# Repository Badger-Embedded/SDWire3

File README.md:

# SDWire3 Flex

## This project is the fork of [SD Swap](https://github.com/Mr-Bossman/SD_Swap) project. The development tool which swaps an SD card between a USB3 card reader and a DUT.

### About

SDWire3 allows reflashing of an SD card connected to the DUT (Device Under Test), without physical contact with the device. The board is designed in such way that it fits into micro SD card slots. Thanks to this, there is no need for special cables with a micro SD adapter, though it may be beneficial to add an extention to avoid accidentally breaking your boards SD connector if someone yanks the cable.

Design is changed to have flex cable instead of solid pcb as dummy sdcard which will be connected to DUT.

**IMPORTANT**

Faster SD cards may not work on some single board computers as the
timing and capacitance on the SBC side is not right.

### Rational

After seeing the [SDWire](https://wiki.tizen.org/SDWire) project I was disappointed by the complexity as well as the lack of USB3. So this project is uses the REALTEK RTS5306E controller which many USB3 to SD adapters use. The chip has power suspend functionality which we can use as a GPIO for switching hosts. The suspend option will shut off the SD cards power but not the controllers; it also has build-in RW protection as to finish writes before switching to the SBC

The SDWire project uses a USB to GPIO chip for this, but they have two power controlled USB ports on the board as well as the above mentioned method.

### Software

To swap the SD card between the host PC and the SBC you run
`sdswap 0` or `sdswap 1`.

`1` is the host PC while `0` is the SBC. You can also chose which device to use if you have multiple attached. To do this run `sdswap 1` to print the found devices and type `sdswap 1-4 1` or another USB number. I have future plans to write this script for Windows and OSX.

```
$ sdswap -h

To switch the SD card to USB run:
sdswap 1
To switch the SD card to SBC run:
sdswap 0
To print the block dev run:
sdswap p

If you have multiple devices run either of the above.
Then run with the last param the same as above:
sdswap $(Your USB number) 0

NOTE:
When printing the block device the script waits until the device exists

Examples:
# sdswap 0
Uisng device /sys/bus/usb/devices/3-4

# sdswap 0
Uisng device /sys/bus/usb/devices/3-4
Already off.

# sdswap p
/dev/sda

# sdswap 0
Multiple devices found! Pass a usb number as param 1...
Usb num: 3-4
Usb num: 3-1

# sdswap 3-1 0
Uisng device /sys/bus/usb/devices/3-1
```

To manually controll the port use:

```
export YOUR_USB_NUM="1-4" #hub1 port4
echo 0 | sudo tee /sys/bus/usb/devices/${YOUR_USB_NUM}/power/autosuspend_delay_ms
echo auto | sudo tee /sys/bus/usb/devices/${YOUR_USB_NUM}/power/control

echo SBC
echo ${YOUR_USB_NUM} | sudo tee /sys/bus/usb/drivers/usb/unbind

echo PC
echo ${YOUR_USB_NUM} | sudo tee /sys/bus/usb/drivers/usb/bind
```

### Hardware

#### LEDs

- D2 is the **red/blue** status LED it will be **blue** when the in passthrough mode, and **red** when the USB3 controller is reading/writing to it.
- D1 is the **yellow** activity LED and blinks when the USB3 controller is reading/writing.
- D3 is the **red** power LED and is active when the USB3 controller has power.

**NOTE**: The **red** power LED will not be on if the USB cable isn't 5V providing power.

### TODO

- Fix SBC side timeing
- Write script for Windows and OSX.
- Edit pick n' place csv
- Label stat leds
- Add use switching regulator
- Add E-Fuse
- Update readme

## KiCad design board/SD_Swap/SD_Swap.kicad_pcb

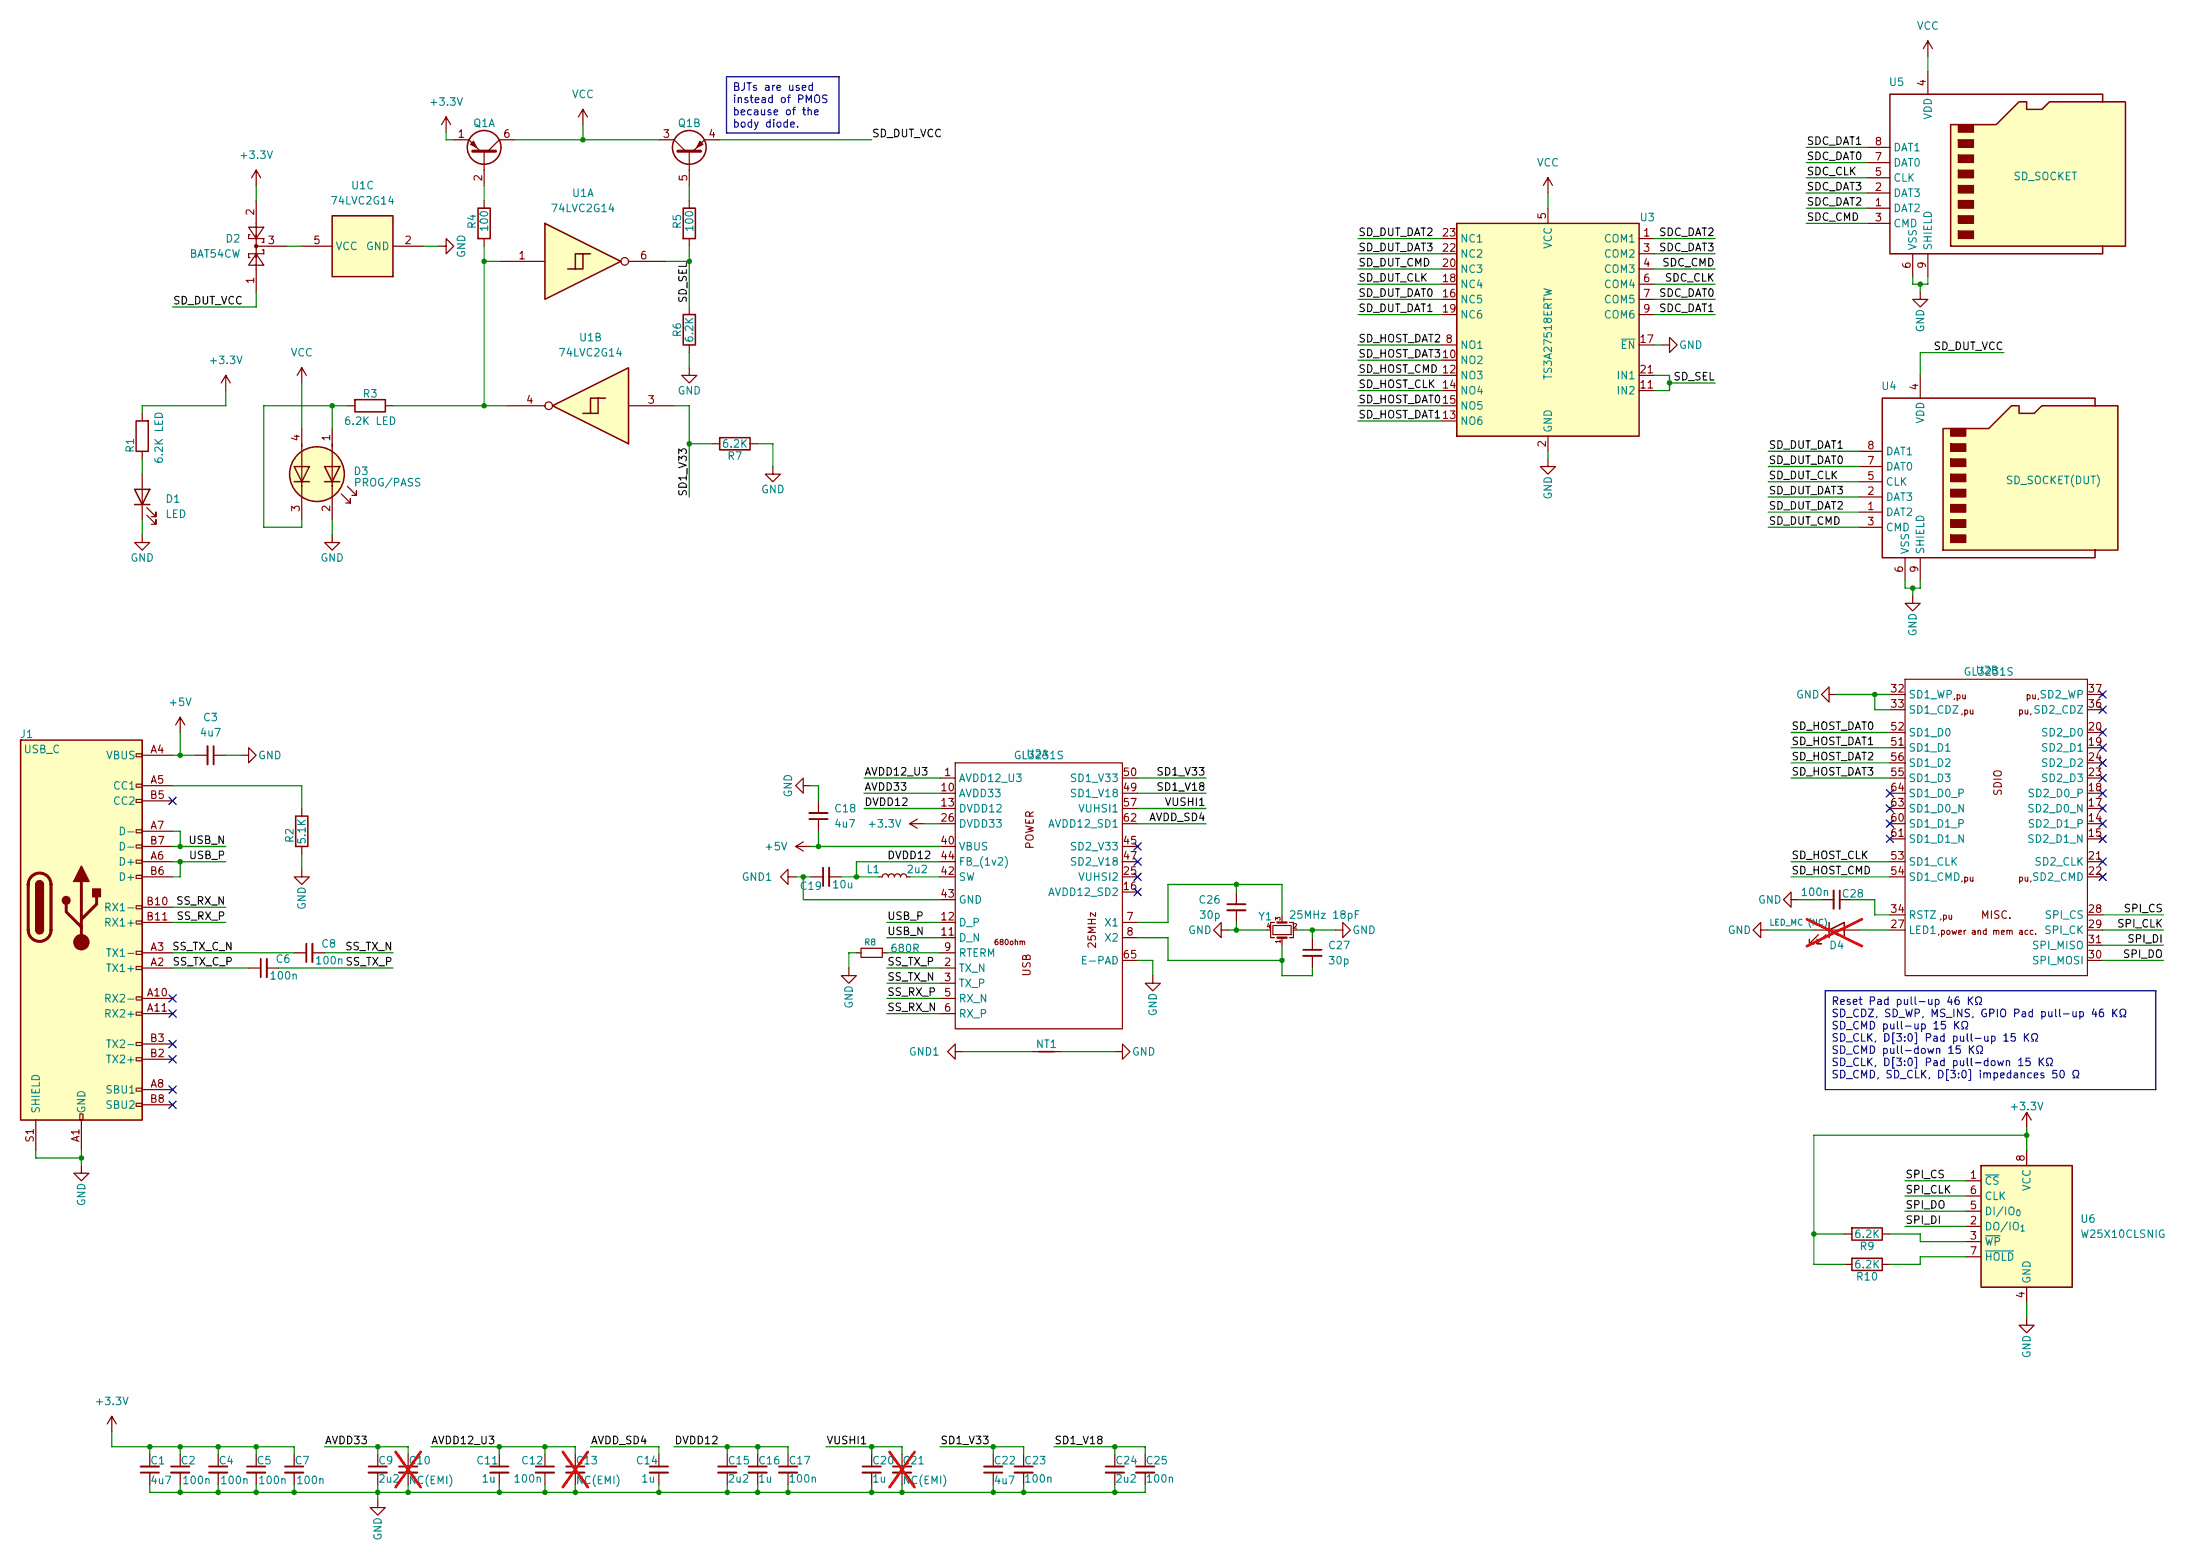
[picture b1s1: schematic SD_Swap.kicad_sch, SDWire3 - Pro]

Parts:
C1, C3, C18, C22: 4u7; C_0402_1005Metric; LCSC C23733
C2, C4, C5, C6, C7, C8, C12, C17, C23, C25, C28: 100n; C_0201_0603Metric; LCSC C66938
C9, C15, C24: 2u2; C_0201_0603Metric; LCSC C76933
C10, C13, C21: NC(EMI); C_0201_0603Metric; not fitted
C11, C14, C16, C20: 1u; C_0402_1005Metric; LCSC C107372
C19: 10u; C_0603_1608Metric; LCSC C19702
C26, C27: 30p; C_0201_0603Metric; LCSC C384980
D1: LED; LED_0402_1005Metric; LCSC C71911
D2: BAT54CW; SOT-323_SC-70; LCSC C57891
D3: PROG/PASS; LED_RGB_1210; LCSC C264332
D4: LED_MC (NC); LED_0603_1608Metric; not fitted
J1: USB_C; USB_C_Receptacle_Amphenol_10137061-00021LF; Part Number 10137061-00021LF; LCSC C3197967
L1: 2u2; L_0402_1005Metric; LCSC C383389
NT1: NetTie_2; NetTie-2_SMD_Pad0.5mm
Q1: Q_Dual_PNP_PNP_E1B1C2E2B2C1; SOT-23-6; LCSC C111730
R1, R3: 6.2K LED; R_0402_1005Metric; LCSC C25915
R2: 5.1K; R_0201_0603Metric; LCSC C100142
R4, R5: 100; R_0201_0603Metric; LCSC C2991668
R6, R7, R9, R10: 6.2K; R_0201_0603Metric; LCSC C180341
R8: 680R; R_0201_0603Metric; LCSC C473509
U1: 74LVC2G14; SOT-363_SC-70-6; LCSC C3294721
U2: GL3231S; QFN-64-1EP_8x8mm_P0.4mm_EP6.5x6.5mm_ThermalVias; LCSC C7435977
U3: TS3A27518ERTW; WQFN-24-1EP_4x4mm_P0.5mm_EP2.6x2.6mm; Part Number TS3A27518ERTW; LCSC C2651937
U4: SD_SOCKET(DUT); 105162-0001; Part Number 105162-0001; LCSC C724031
U5: SD_SOCKET; 105162-0001; Part Number 105162-0001; LCSC C724031
U6: W25X10CLSNIG; SOIC-8_3.9x4.9mm_P1.27mm; LCSC C164120
Y1: 25MHz 18pF; Crystal_SMD_2520-4Pin_2.5x2.0mm; LCSC C255956

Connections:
+3.3V: C1.2, C2.1, C4.1, C5.1, C7.1, D2.2, Q1.1 (E1), R1.2, R9.2, R10.2, U2.26 (DVDD33), U2.39 (DVDD33), U2.46 (DVDD33), U2.48 (DVDD33), U2.58 (DVDD33), U6.8 (VCC)
+5V: C3.2, C18.1, J1.A4 (VBUS), J1.A9 (VBUS), J1.B4 (VBUS), J1.B9 (VBUS), U2.40 (VBUS), U2.41 (VBUS)
/AVDD12_U3: C11.1, C12.1, C13.1, U2.1 (AVDD12_U3), U2.4 (AVDD12_U3)
/AVDD33: C9.1, C10.1, U2.10 (AVDD33)
/AVDD_SD4: C14.1, U2.62 (AVDD12_SD1)
/DVDD12: C15.1, C16.1, C17.1, C19.2, L1.1, U2.13 (DVDD12), U2.38 (DVDD12), U2.44 (FB_(1v2)), U2.59 (DVDD12)
/SD1_V18: C24.1, C25.1, U2.49 (SD1_V18)
/SD1_V33: C22.2, C23.1, R7.2, U1.3, U2.50 (SD1_V33)
/SDC_CLK: U3.6 (COM4), U5.5 (CLK)
/SDC_CMD: U3.4 (COM3), U5.3 (CMD)
/SDC_DAT0: U3.7 (COM5), U5.7 (DAT0)
/SDC_DAT1: U3.9 (COM6), U5.8 (DAT1)
/SDC_DAT2: U3.1 (COM1), U5.1 (DAT2)
/SDC_DAT3: U3.3 (COM2), U5.2 (DAT3)
/SD_DUT_CLK: U3.18 (NC4), U4.5 (CLK)
/SD_DUT_CMD: U3.20 (NC3), U4.3 (CMD)
/SD_DUT_DAT0: U3.16 (NC5), U4.7 (DAT0)
/SD_DUT_DAT1: U3.19 (NC6), U4.8 (DAT1)
/SD_DUT_DAT2: U3.23 (NC1), U4.1 (DAT2)
/SD_DUT_DAT3: U3.22 (NC2), U4.2 (DAT3)
/SD_DUT_VCC: D2.1, Q1.4 (E2), U4.4 (VDD)
/SD_HOST_CLK: U2.53 (SD1_CLK), U3.14 (NO4)
/SD_HOST_CMD: U2.54 (SD1_CMD), U3.12 (NO3)
/SD_HOST_DAT0: U2.52 (SD1_D0), U3.15 (NO5)
/SD_HOST_DAT1: U2.51 (SD1_D1), U3.13 (NO6)
/SD_HOST_DAT2: U2.56 (SD1_D2), U3.8 (NO1)
/SD_HOST_DAT3: U2.55 (SD1_D3), U3.10 (NO2)
/SD_SEL: R5.2, R6.2, U1.6, U3.11 (IN2), U3.21 (IN1)
/SPI_CLK: U2.29 (SPI_CK), U6.6 (CLK)
/SPI_CS: U2.28 (SPI_CS), U6.1 (~CS)
/SPI_DI: U2.31 (SPI_MISO), U6.2 (DO/IO_{1})
/SPI_DO: U2.30 (SPI_MOSI), U6.5 (DI/IO_{0})
/SS_RX_N: J1.B10 (RX1-), U2.6 (RX_P)
/SS_RX_P: J1.B11 (RX1+), U2.5 (RX_N)
/SS_TX_C_N: C8.1, J1.A3 (TX1-)
/SS_TX_C_P: C6.1, J1.A2 (TX1+)
/SS_TX_N: C8.2, U2.3 (TX_P)
/SS_TX_P: C6.2, U2.2 (TX_N)
/USB_N: J1.A7 (D-), J1.B7 (D-), U2.11 (D_N)
/USB_P: J1.A6 (D+), J1.B6 (D+), U2.12 (D_P)
/VUSHI1: C20.1, C21.1, U2.57 (VUHSI1)
GND: C1.1, C2.2, C3.1, C4.2, C5.2, C7.2, C9.2, C10.2, C11.2, C12.2, C13.2, C14.2, C15.2, C16.2, C17.2, C18.2, C20.2, C21.2, C22.1, C23.2, C24.2, C25.2, C26.2, C27.1, C28.2, D1.1 (K), D3.2 (K1), D4.1 (K), J1.A1 (GND), J1.A12 (GND), J1.B1 (GND), J1.B12 (GND), J1.S1 (SHIELD), NT1.2, R2.2, R6.1, R7.1, R8.2, U1.2 (GND), U2.32 (SD1_WP), U2.33 (SD1_CDZ), U2.65 (E-PAD), U3.2 (GND), U3.17 (~EN), U3.25 (GND), U4.6 (VSS), U4.9 (SHIELD), U4.10 (SHIELD), U4.11 (SHIELD), U4.12 (SHIELD), U4.13 (SHIELD), U4.14 (SHIELD), U4.15 (SHIELD), U5.6 (VSS), U5.9 (SHIELD), U5.10 (SHIELD), U5.11 (SHIELD), U5.12 (SHIELD), U5.13 (SHIELD), U5.14 (SHIELD), U5.15 (SHIELD), U6.4 (GND), Y1.2, Y1.4
GND1: C19.1, NT1.1, U2.43 (GND)
unnamed: D1.2 (A), R1.1
unnamed: D3.1 (A1), D3.3 (K2), R3.2
unnamed: D4.2 (A), U2.27 (LED1)
unnamed: J1.A5 (CC1), R2.1
unnamed: Q1.2 (B1), R4.1
unnamed: Q1.5 (B2), R5.1
unnamed: R3.1, R4.2, U1.1, U1.4
unnamed: D2.3, U1.5 (VCC)
unnamed: R8.1, U2.9 (RTERM)
unnamed: L1.2, U2.42 (SW)
unnamed: C26.1, U2.7 (X1), Y1.3
unnamed: C27.2, U2.8 (X2), Y1.1
unnamed: C28.1, U2.34 (RSTZ)
unnamed: R10.1, U6.7 (~HOLD)
unnamed: R9.1, U6.3 (~WP)
VCC: D3.4 (A2), Q1.3 (C2), Q1.6 (C1), U3.5 (VCC), U5.4 (VDD)

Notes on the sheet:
BJTs are used instead of PMOS because of the body diode.
Reset Pad pull-up 46 KΩ SD_CDZ, SD_WP, MS_INS, GPIO Pad pull-up 46 KΩ SD_CMD pull-up 15 KΩ SD_CLK, D[3:0] Pad pull-up 15 KΩ SD_CMD pull-down 15 KΩ SD_CLK, D[3:0] Pad pull-down 15 KΩ SD_CMD, SD_CLK, D[3:0] impedances 50 Ω

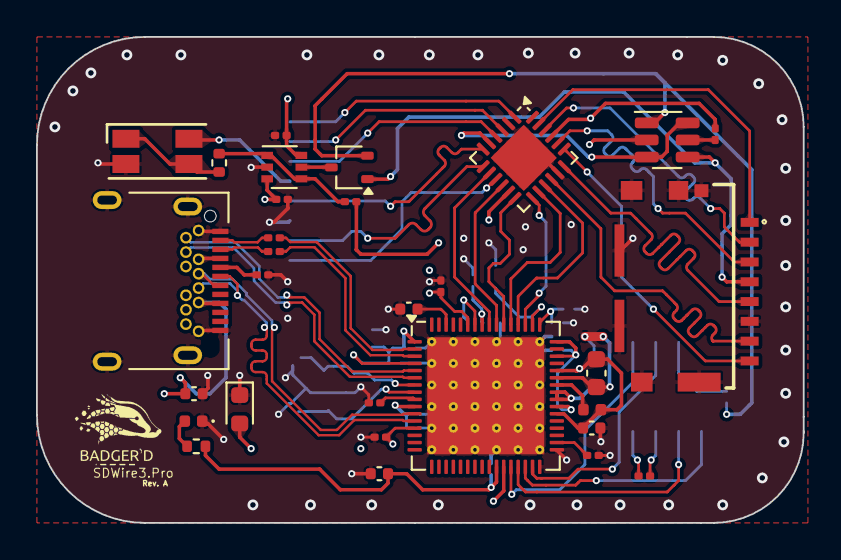
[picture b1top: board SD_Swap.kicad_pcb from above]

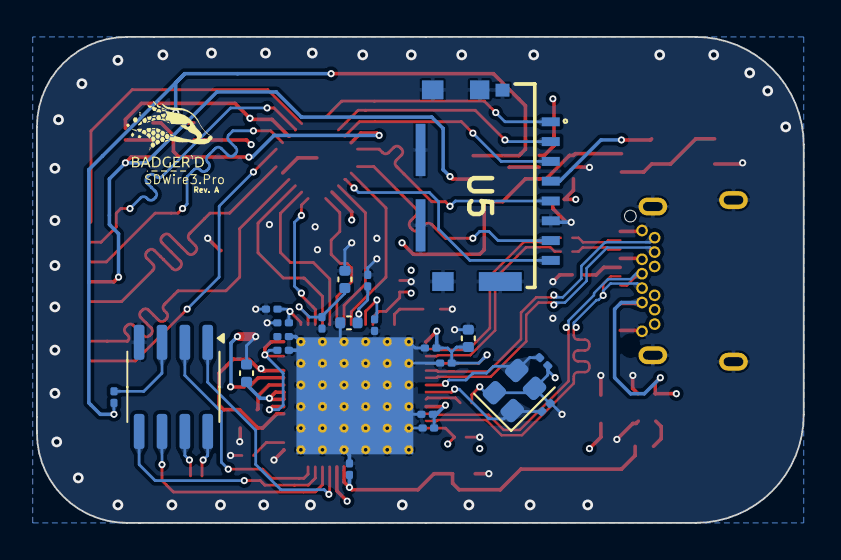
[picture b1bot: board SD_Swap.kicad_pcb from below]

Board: 4 copper layers, 42.6 x 27.0 mm, 53 parts (22 on the bottom side), 59 nets.

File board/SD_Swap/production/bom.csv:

Designator,Footprint,Quantity,Value,LCSC Part #
"C1, C18, C22, C3",0402,4,4u7,C23733
"C11, C14, C16, C20",0402,4,1u,C107372
"C12, C17, C2, C23, C25, C28, C4, C5, C6, C7, C8",0201,11,100n,C66938
"C15, C24, C9",0201,3,2u2,C76933
C19,0603,1,10u,C19702
"C26, C27",0201,2,30p,C384980
D1,0402,1,LED,C71911
D2,SOT-323_SC-70,1,BAT54CW,C57891
D3,LED_RGB_1210,1,PROG/PASS,C264332
J1,USB_C_Receptacle_Amphenol_10137061-00021LF,1,USB_C,C3197967
L1,0402,1,2u2,C383389
Q1,SOT-23-6,1,Q_Dual_PNP_PNP_E1B1C2E2B2C1,C111730
"R1, R3",0402,2,6.2K LED,C25915
"R10, R6, R7, R9",0201,4,6.2K,C295814
R2,0201,1,5.1K,C100142
"R4, R5",0201,2,100,C2991668
R8,0201,1,680R,C473509
U1,SOT-363_SC-70-6,1,74LVC2G14,C3294721
U2,QFN-64-1EP_8x8mm_P0.4mm_EP6.5x6.5mm_ThermalVias,1,GL3231S,C7435977
U3,WQFN-24-1EP_4x4mm_P0.5mm_EP2.6x2.6mm,1,TS3A27518ERTW,C2651937
U4,105162-0001,1,SD_SOCKET(DUT),C724031
U5,105162-0001,1,SD_SOCKET,C724031
U6,SOIC-8_3.9x4.9mm_P1.27mm,1,W25X10CLSNIG,C164120
Y1,Crystal_SMD_2520-4Pin_2.5x2.0mm,1,25MHz 18pF,C255956

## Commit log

2025-01-27 Update silkscreen to include logo and revision number
2025-01-27 add ffc 8P footprint
2025-01-27 squash! add ffc 8P footprint
2025-02-25 update part numbers
2026-05-30 Inital commit for publication
    add FFC connector to pcb instead of dummy sd
    update readme
    pro: create symbos for gl3231s
    pro: update gl3231s power circuit
    pro: add decoupling capacitors
    pro: add spi flash for gl3231s
